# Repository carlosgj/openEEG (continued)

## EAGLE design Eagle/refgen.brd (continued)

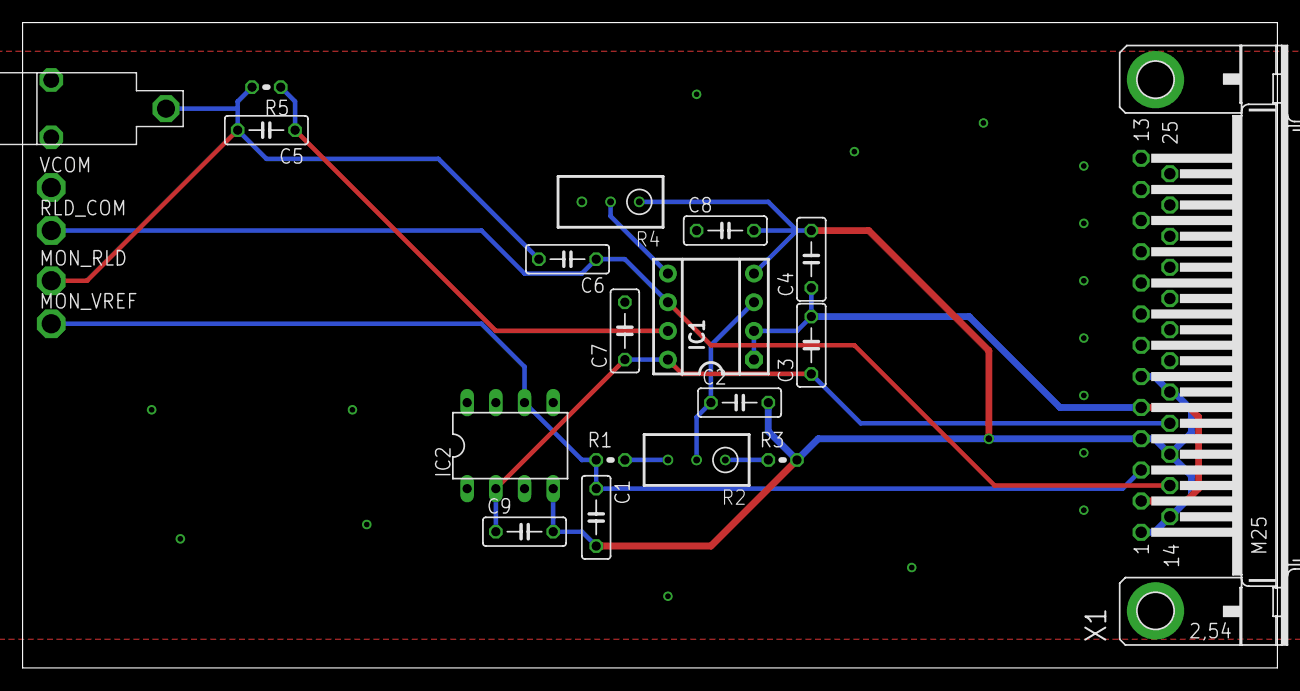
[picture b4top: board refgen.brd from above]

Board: 2 copper layers, 111.1 x 57.1 mm, 22 parts (0 on the bottom side), 11 nets.

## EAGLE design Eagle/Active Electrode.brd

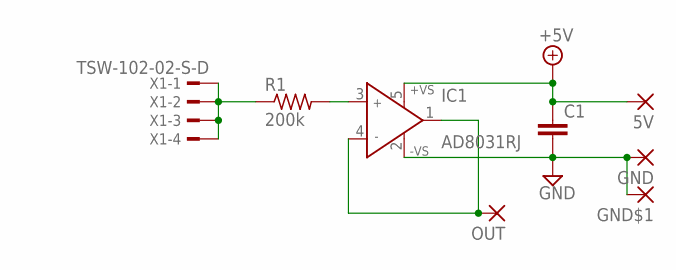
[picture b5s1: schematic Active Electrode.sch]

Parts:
5V: 1,6/0,9
C1: C-EUC1206; C1206
GND: 1,6/0,9
GND$1: 1,6/0,9
IC1: AD8031RJ; SOT23-5
OUT: 1,6/0,9
R1: 200k; M1206
X1: TSW-102-02-S-D

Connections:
+5V: 5V.1, C1.1, IC1.5 (+VS)
GND: C1.2, GND.1, GND$1.1, IC1.2 (-VS)
unnamed: R1.1, X1.1, X1.2, X1.3, X1.4
unnamed: IC1.3 (IN+), R1.2
unnamed: IC1.1 (OUT), IC1.4 (IN-), OUT.1

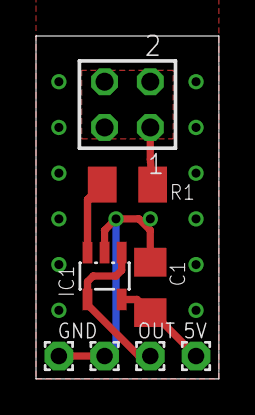
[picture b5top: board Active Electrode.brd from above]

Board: 2 copper layers, 10.2 x 19.1 mm, 8 parts (0 on the bottom side), 5 nets.

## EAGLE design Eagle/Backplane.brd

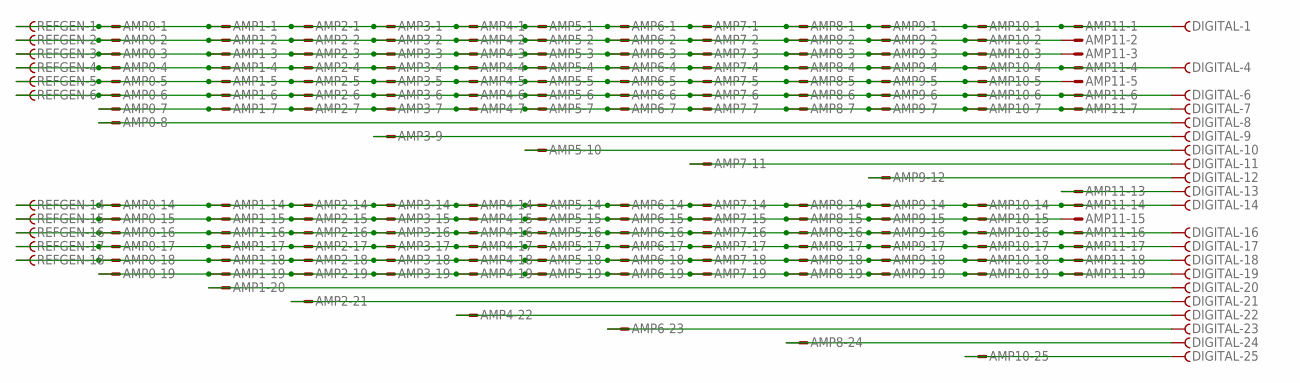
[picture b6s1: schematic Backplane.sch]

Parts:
AMP0, AMP1, AMP2, AMP3, AMP4, AMP5, AMP6, AMP7, AMP8, AMP9, AMP10, AMP11: M25VPS; M25VP
DIGITAL: F25VPS; F25VP
REFGEN: F25VPS; F25VP

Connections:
unnamed: AMP0.1, AMP1.1, AMP2.1, AMP3.1, AMP4.1, AMP5.1, AMP6.1, AMP7.1, AMP8.1, AMP9.1, AMP10.1, AMP11.1, DIGITAL.1, REFGEN.1
unnamed: AMP0.2, AMP1.2, AMP2.2, AMP3.2, AMP4.2, AMP5.2, AMP6.2, AMP7.2, AMP8.2, AMP9.2, AMP10.2, AMP11.2, REFGEN.2
unnamed: AMP0.3, AMP1.3, AMP2.3, AMP3.3, AMP4.3, AMP5.3, AMP6.3, AMP7.3, AMP8.3, AMP9.3, AMP10.3, AMP11.3, REFGEN.3
unnamed: AMP0.4, AMP1.4, AMP2.4, AMP3.4, AMP4.4, AMP5.4, AMP6.4, AMP7.4, AMP8.4, AMP9.4, AMP10.4, AMP11.4, DIGITAL.4, REFGEN.4
unnamed: AMP0.5, AMP1.5, AMP2.5, AMP3.5, AMP4.5, AMP5.5, AMP6.5, AMP7.5, AMP8.5, AMP9.5, AMP10.5, AMP11.5, REFGEN.5
unnamed: AMP0.8, DIGITAL.8
unnamed: AMP3.9, DIGITAL.9
unnamed: AMP4.22, DIGITAL.22
unnamed: AMP2.21, DIGITAL.21
unnamed: AMP1.20, DIGITAL.20
unnamed: AMP0.19, AMP1.19, AMP2.19, AMP3.19, AMP4.19, AMP5.19, AMP6.19, AMP7.19, AMP8.19, AMP9.19, AMP10.19, AMP11.19, DIGITAL.19
unnamed: AMP5.10, DIGITAL.10
unnamed: AMP0.6, AMP1.6, AMP2.6, AMP3.6, AMP4.6, AMP5.6, AMP6.6, AMP7.6, AMP8.6, AMP9.6, AMP10.6, AMP11.6, DIGITAL.6, REFGEN.6
unnamed: AMP0.7, AMP1.7, AMP2.7, AMP3.7, AMP4.7, AMP5.7, AMP6.7, AMP7.7, AMP8.7, AMP9.7, AMP10.7, AMP11.7, DIGITAL.7
unnamed: AMP6.23, DIGITAL.23
unnamed: AMP7.11, DIGITAL.11
unnamed: AMP8.24, DIGITAL.24
unnamed: AMP9.12, DIGITAL.12
unnamed: AMP0.14, AMP1.14, AMP2.14, AMP3.14, AMP4.14, AMP5.14, AMP6.14, AMP7.14, AMP8.14, AMP9.14, AMP10.14, AMP11.14, DIGITAL.14, REFGEN.14
unnamed: AMP0.15, AMP1.15, AMP2.15, AMP3.15, AMP4.15, AMP5.15, AMP6.15, AMP7.15, AMP8.15, AMP9.15, AMP10.15, AMP11.15, REFGEN.15
unnamed: AMP10.25, DIGITAL.25
unnamed: AMP0.16, AMP1.16, AMP2.16, AMP3.16, AMP4.16, AMP5.16, AMP6.16, AMP7.16, AMP8.16, AMP9.16, AMP10.16, AMP11.16, DIGITAL.16, REFGEN.16
unnamed: AMP0.17, AMP1.17, AMP2.17, AMP3.17, AMP4.17, AMP5.17, AMP6.17, AMP7.17, AMP8.17, AMP9.17, AMP10.17, AMP11.17, DIGITAL.17, REFGEN.17
unnamed: AMP0.18, AMP1.18, AMP2.18, AMP3.18, AMP4.18, AMP5.18, AMP6.18, AMP7.18, AMP8.18, AMP9.18, AMP10.18, AMP11.18, DIGITAL.18, REFGEN.18
unnamed: AMP11.13, DIGITAL.13

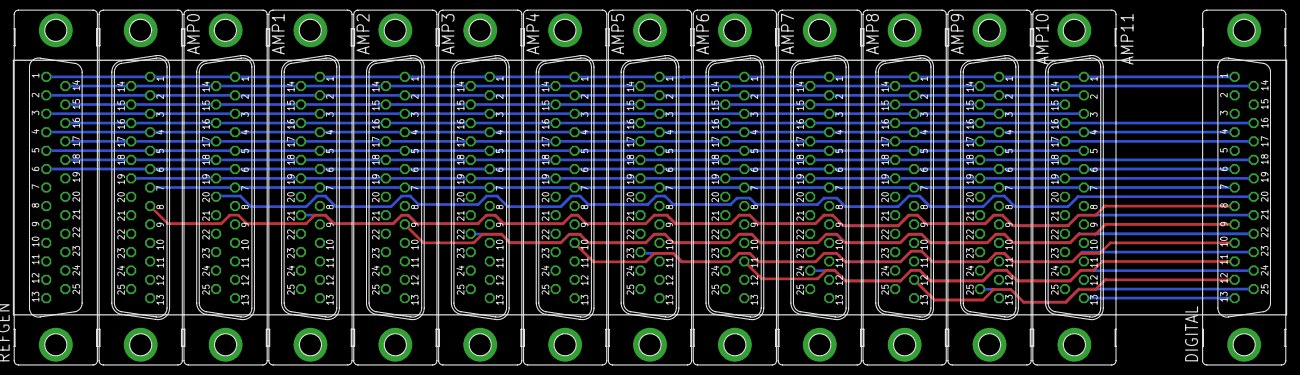
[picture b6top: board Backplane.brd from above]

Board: 2 copper layers, 190.5 x 38.1 mm, 14 parts (0 on the bottom side), 25 nets.

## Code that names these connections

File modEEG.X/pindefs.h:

#ifndef PINDEFS_H
#define	PINDEFS_H

#include <xc.h> // include processor files - each processor file is guarded.  

#define PORT_PIN_SCK PORTCbits.RC0
#define TRIS_PIN_SCK TRISCbits.TRISC0

#define PORT_PIN_CNV PORTCbits.RC1
#define TRIS_PIN_CNV TRISCbits.TRISC1

#define PORT_PIN_RTS PORTCbits.RC2
#define TRIS_PIN_RTS TRISCbits.RC2

#define PORT_PIN_USB_DETECT PORTAbits.RA0
#define TRIS_PIN_USB_DETECT TRISAbits.RA0

#endif	/* XC_HEADER_TEMPLATE_H */

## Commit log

2016-08-13 Inital
2016-08-14 Upconvert
2016-08-15 New version!
2016-10-25 Added control board
2016-10-25 Finished digital board
2016-10-31 Switched to DB25
2016-10-31 Finished up chanes to DB25
2016-11-01 Added optoisolators
2016-11-02 Corrected connector positions
2016-11-03 Added DIN 42802 jacks & power for active electrodes
2016-11-03 Active electrodes
2016-11-03 Updated backplane spacing
2016-11-03 Added indicator LEDs
2016-11-03 Updated resistor values
2016-11-03 Deprecated
2016-11-06 Code
2016-11-06 Added 232 interface
2016-11-06 Code work
2016-11-07 More code work
2016-11-07 Changed USB to differential pair
2016-11-07 Added ethernet module
2016-11-07 Added level shifting
2016-11-08 Added RTS
2016-11-08 Shrunk boards
2016-11-08 Board shrink
2016-11-08 Board updates
2016-11-22 Changed to DB-15 connector
2016-11-22 Added mounting holes
2016-12-02 Added connection monitor
2016-12-14 Board updates (jumpers)
2016-12-14 Part numbers
2017-01-04 Packages
